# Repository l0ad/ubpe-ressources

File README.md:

# Ressources UBPE  

Ce dépôt contient des ressources (cartes capteurs, ...), utilisables dans le cadre de l'opération *Un ballon pour l'école* (UBPE) proposée par l'association [Planète-Sciences](https://www.planete-sciences.org/national/).

- [Cartes](./Cartes/README.md) 
	- capteurs analogiques
	- adaptateur pour étalonnage
	- conversion d'alimentation
	- ...
- ...

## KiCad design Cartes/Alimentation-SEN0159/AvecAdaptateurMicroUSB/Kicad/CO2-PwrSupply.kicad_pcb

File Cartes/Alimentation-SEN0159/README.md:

# Carte d'alimentation pour capteur CO2 SEN-0159

Version 1.1, novembre 2023.

*N.B.: les circuits utilisent les symboles/empreintes/modèles Kicad de la librairie additionnelle L0AD qui peut être téléchargée depuis ce [dépôt](https://github.com/l0ad/L0AD-kicad-library) et installée depuis le gestionnaire d'extensions Kicad (par fichier).* 

Cette carte est destinée à l'**alimentation** d'un module [module capteur de CO2 SEN0159](https://wiki.dfrobot.com/CO2_Sensor_SKU_SEN0159), et sa **connexion** à une carte *Kikiwi* (ou autre microcontrôleur).

Comme le capteur CO2 a besoin de préchauffer (et donc d'être alimenté) pendant plusieurs dizaines de minutes, il est ainsi possible d'alimenter le capteur temporairement avec une batterie externe via le port USB avant de le brancher de manière permanente à l'alimentation externe.

## Schéma de principe

La carte peut être alimentée soit via le connecteur externe (alimentation > 6V) ou directement en USB (5V). 

Le module *SEN-0159* est connecté via le connecteur JST-XH 3 points.

La carte est reliée au *Kikiwi* via le connecteur JST-XH 2 points (masse et signal uniquement, l'alimentation du capteur n'est pas prise du Kikiwi mais fournie par la carte).

La carte est conçue en deux variantes :

- avec un **connecteur MicroUSB** CMS
	- Le **projet Kicad** (>= v6.0) est disponible dans le répertoire [Kicad](./AvecConnecteurUSB/Kicad).
	- Les **fichiers de fabrication** sont disponibles dans le répertoire [Gerber](./AvecConnecteurUSB/Gerber). 
- avec un **adaptateur microUSB vers 2.54mm**, pour utiliser ce [module](https://www.amazon.fr/dp/B08ZML34CK).
	- Le **projet Kicad** (>= v6.0) est disponible dans le répertoire [Kicad](./AvecAdaptateurMicroUSB/Kicad).
	- Les **fichiers de fabrication** sont disponibles dans le répertoire [Gerber](./AvecAdaptateurMicroUSB/Gerber).

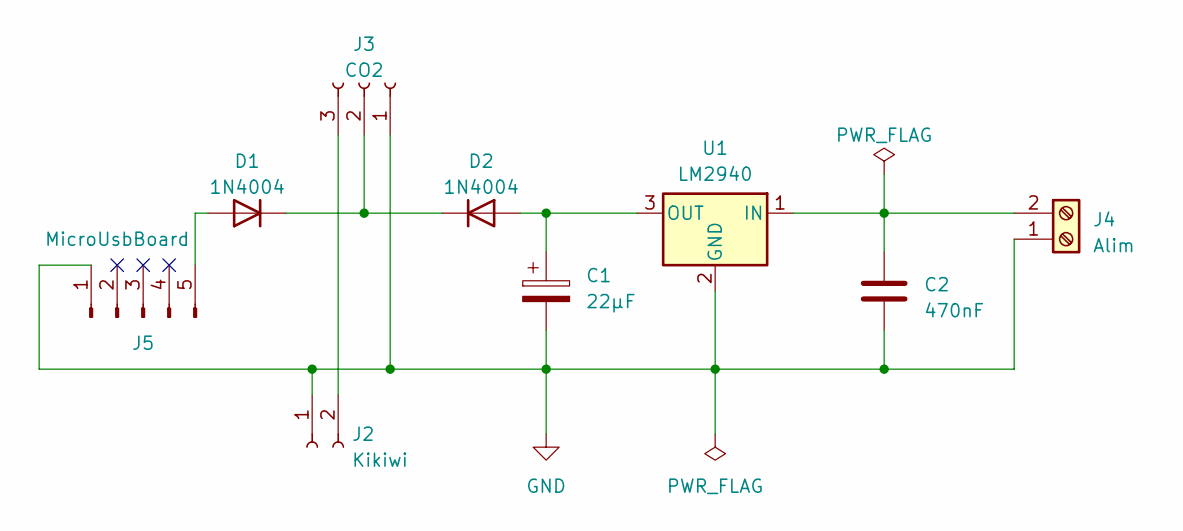
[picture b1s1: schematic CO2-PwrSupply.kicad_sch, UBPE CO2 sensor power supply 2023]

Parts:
C1: 22µF; CP_Radial_D5.0mm_P2.50mm
C2: 470nF; C_Rect_L7.0mm_W6.0mm_P5.00mm
D1, D2: 1N4004; D_DO-41_SOD81_P10.16mm_Horizontal
J2: Kikiwi; JST_XH_B2B-XH-A_1x02_P2.50mm_Vertical
J3: CO2; JST_XH_B3B-XH-A_1x03_P2.50mm_Vertical
J4: Alim; TerminalBlock_Phoenix_MKDS-1,5-2-5.08_1x02_P5.08mm_Horizont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
J5: MicroUsbBoard; PinHeader_1x05_P2.54mm_Vertical
U1: LM2940; TO-220-3_Horizontal_TabDown

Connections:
GND: C1.2, C2.2, J2.1, J3.1, J4.1, J5.1, U1.2 (GND)
unnamed: D1.2 (A), J5.5
unnamed: D1.1 (K), D2.1 (K), J3.2
unnamed: C1.1, D2.2 (A), U1.3 (OUT)
unnamed: J2.2, J3.3
unnamed: C2.1, J4.2, U1.1 (IN)

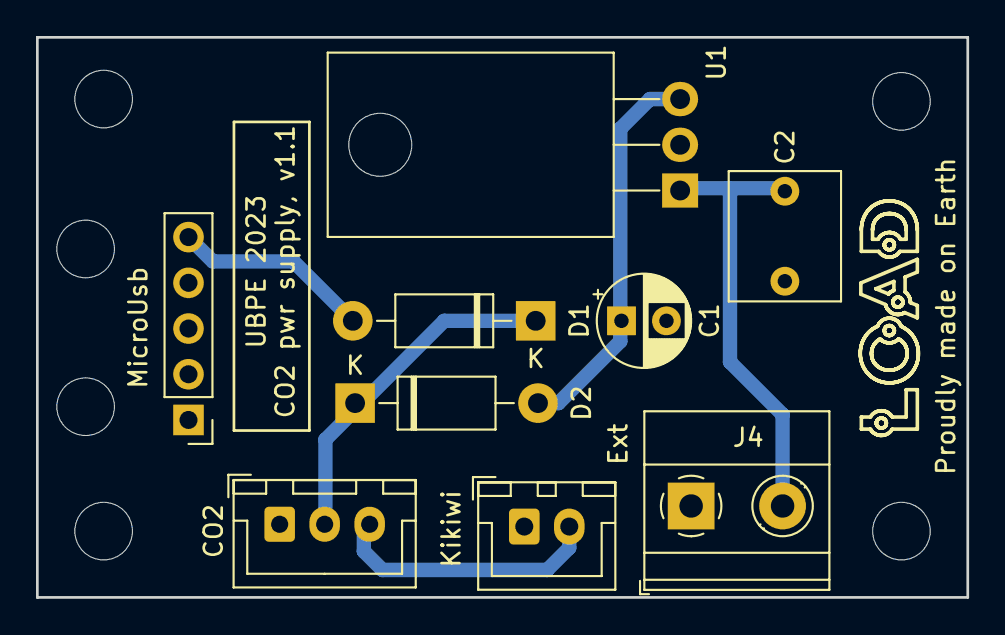
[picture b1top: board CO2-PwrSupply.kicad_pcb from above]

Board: 2 copper layers, 51.7 x 31.1 mm, 11 parts (1 on the bottom side), 6 nets.

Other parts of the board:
M3-1, M3-2: MountingHole_3.2mm_M3_ISO14580

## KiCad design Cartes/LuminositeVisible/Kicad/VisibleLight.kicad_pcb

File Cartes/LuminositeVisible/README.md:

# Capteur de luminosité (visible)

Version 1.1, novembre 2023.

*N.B.: les circuits utilisent les symboles/empreintes/modèles Kicad de la librairie additionnelle L0AD qui peut être téléchargée depuis ce [dépôt](https://github.com/l0ad/L0AD-kicad-library) et installée depuis le gestionnaire d'extensions Kicad (par fichier).* 

Cette carte peut être utilisée pour la mesure (analogique) luminosité (visible, proche IR),

## Schéma de principe

Le capteur utilisé est une **photodiode BPW34** (voir [datasheet](https://www.vishay.com/docs/81521/bpw34.pdf)

La tension d'alimentation est 3.3V, la connectique est de type JST-XH 3 points pour la liaison avec la carte Tenum/Planete-sciences *Kikiwi*, un micro-controleur ou un adaptateur destiné à l'étalonnage.

La diode peut être soit soudée sur la carte (surélevée et/ou montée à l'envers pour dépasser du dos de la carte) ou déportée à l'aide du connecteur 2 broches.

Les connecteurs peuvent être au choix horizontaux ou verticaux.

- Le **projet Kicad** (>= v6.0) est disponible dans le répertoire [Kicad](./Kicad).
- Les **fichiers de fabrication** sont disponibles dans le répertoire [Gerber](./Gerber).

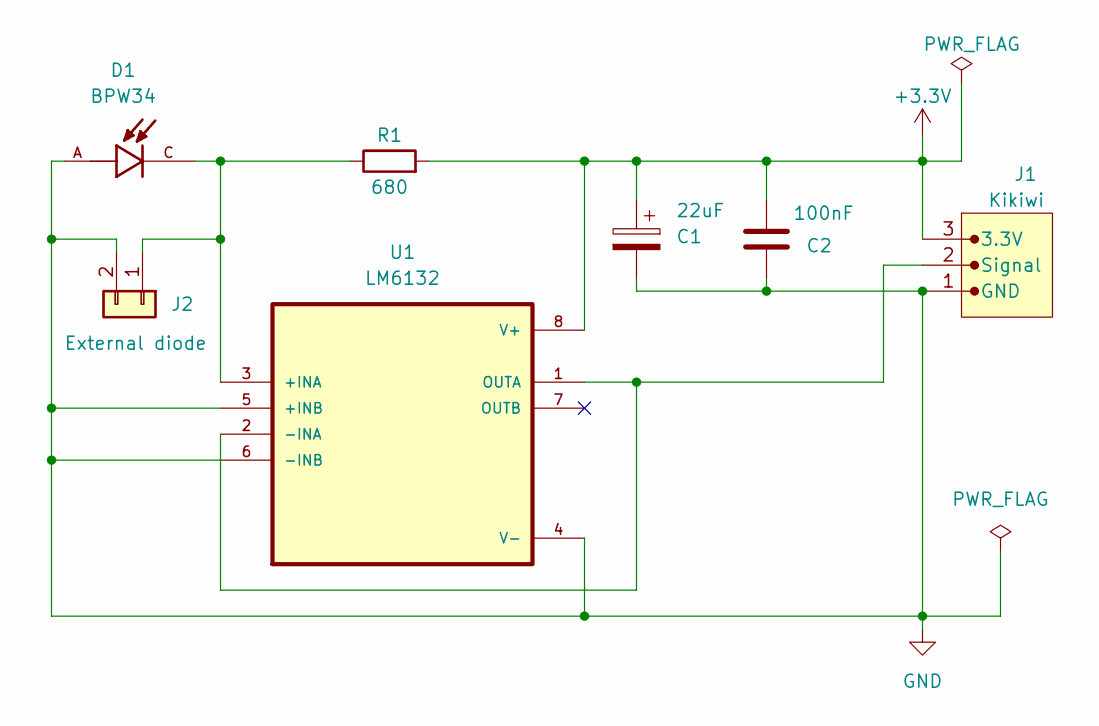
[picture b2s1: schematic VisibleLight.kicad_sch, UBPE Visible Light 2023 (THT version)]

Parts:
C1: 22uF; CP_Radial_D5.0mm_P2.50mm
C2: 100nF; C_Rect_L7.0mm_W2.5mm_P5.00mm
D1: BPW34; PARTREV 2.1
J1: Kikiwi; JST_XH_B3B-XH-AM_1x03_P2.50mm_Vertical
J2: External diode; JST_XH_B2B-XH-A_1x02_P2.50mm_Vertical
R1: 680; R_Axial_DIN0204_L3.6mm_D1.6mm_P7.62mm_Horizontal
U1: LM6132; DIP-8_W7.62mm

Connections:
+3.3V: C1.1, C2.2, J1.3 (3.3V), R1.2, U1.8 (V+)
GND: C1.2, C2.1, D1.A, J1.1 (GND), J2.2, U1.4 (V-), U1.5 (+INB), U1.6 (-INB)
unnamed: J1.2 (Signal), U1.1 (OUTA), U1.2 (-INA)
unnamed: D1.C, J2.1, R1.1, U1.3 (+INA)

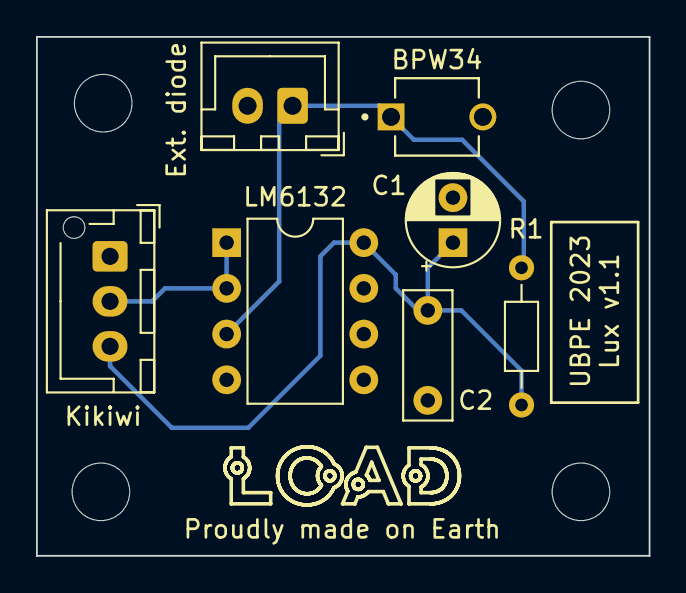
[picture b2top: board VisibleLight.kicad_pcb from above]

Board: 2 copper layers, 34.0 x 28.8 mm, 7 parts (0 on the bottom side), 4 nets.

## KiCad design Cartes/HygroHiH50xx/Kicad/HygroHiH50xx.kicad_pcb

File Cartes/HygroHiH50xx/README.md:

# Carte capteur d'humidité (HiH-50xx)

Version 1.1, novembre 2023.

*N.B.: les circuits utilisent les symboles/empreintes/modèles Kicad de la librairie additionnelle L0AD qui peut être téléchargée depuis ce [dépôt](https://github.com/l0ad/L0AD-kicad-library) et installée depuis le gestionnaire d'extensions Kicad (par fichier).* 

Cette carte peut être utilisée pour la mesure (analogique) d'humidité relative de l'air.

## Schéma de principe

Le capteur utilisé est de type **HiH-50xx** (voir [datasheet](https://prod-edam.honeywell.com/content/dam/honeywell-edam/sps/siot/fr-fr/products/sensors/humidity-with-temperature-sensors/hih-5030-5031-series/documents/sps-siot-hih5030-5031-series-product-sheet-009050-2-en-ciid-49692.pdf))

La tension d'alimentation est 3.3V, la connectique est de type JST-XH 3 points pour la liaison avec la carte Tenum/Planete-sciences *Kikiwi*, un micro-controleur ou un adaptateur destiné à l'étalonnage.

- Le **projet Kicad** (>= v6.0) est disponible dans le répertoire [Kicad](./Kicad).
- Les **fichiers de fabrication** sont disponibles dans le répertoire [Gerber](./Gerber).

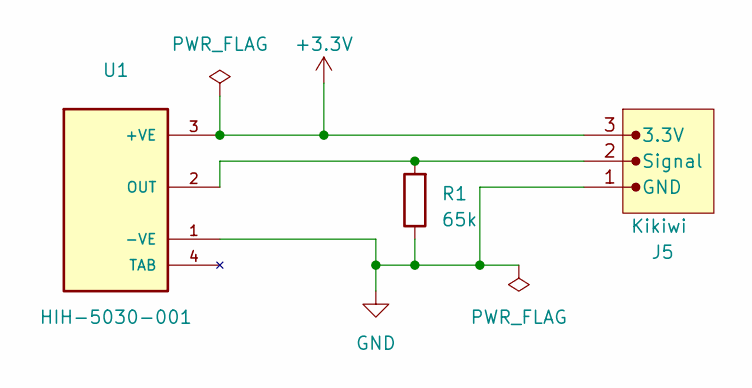
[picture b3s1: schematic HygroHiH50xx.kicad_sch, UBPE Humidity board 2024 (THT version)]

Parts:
J5: Kikiwi; JST_XH_B3B-XH-A_1x03_P2.50mm_Vertical
R1: 65k; R_Axial_DIN0207_L6.3mm_D2.5mm_P10.16mm_Horizontal
U1: HIH-5030-001; HiH-5030

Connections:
+3.3V: J5.3, U1.3 (+VE)
GND: J5.1, R1.1, U1.1 (-VE)
unnamed: J5.2, R1.2, U1.2 (OUT)

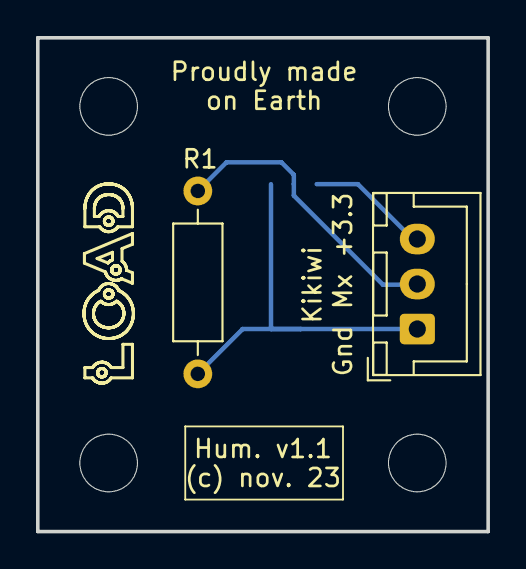
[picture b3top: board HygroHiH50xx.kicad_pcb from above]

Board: 2 copper layers, 25.0 x 27.4 mm, 3 parts (1 on the bottom side), 3 nets.

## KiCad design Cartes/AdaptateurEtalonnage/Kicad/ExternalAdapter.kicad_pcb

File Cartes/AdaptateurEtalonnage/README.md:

# Adaptateur pour l'étalonnage

Version 1.0, novembre 2023.

*N.B.: les circuits utilisent les symboles/empreintes/modèles Kicad de la librairie additionnelle L0AD qui peut être téléchargée depuis ce [dépôt](https://github.com/l0ad/L0AD-kicad-library) et installée depuis le gestionnaire d'extensions Kicad (par fichier).* 

Cette carte est destinée à l'étalonnage des capteurs analogiques, elle ne comporte aucun composant actif mais seulement de la connectique.

L'alimentation s'effectue en 3.3V, la connectique *JST-XH* 3 points permet la liaison avec le capteur, la connectique *SLB4* 1 point permet l'alimentation et la prise de mesure.

- Le **projet Kicad** (>= v6.0) est disponible dans le répertoire [Kicad](./Kicad).
- Les **fichiers de fabrication** sont disponibles dans le répertoire [Gerber](./Gerber).

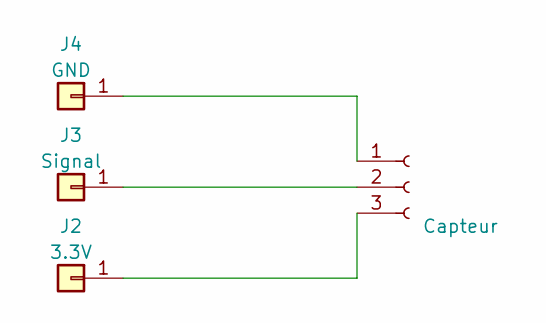
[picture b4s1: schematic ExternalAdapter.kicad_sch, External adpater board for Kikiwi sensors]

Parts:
J1: Capteur; JST_XH_S3B-XH-A-1_1x03_P2.50mm_Horizontal
J2: 3.3V; SolderWire-1.5sqmm_1x01_D1.7mm_OD3.9mm
J3: Signal; SolderWire-1.5sqmm_1x01_D1.7mm_OD3.9mm
J4: GND; SolderWire-1.5sqmm_1x01_D1.7mm_OD3.9mm

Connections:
unnamed: J1.1, J4.1
unnamed: J1.2, J3.1
unnamed: J1.3, J2.1

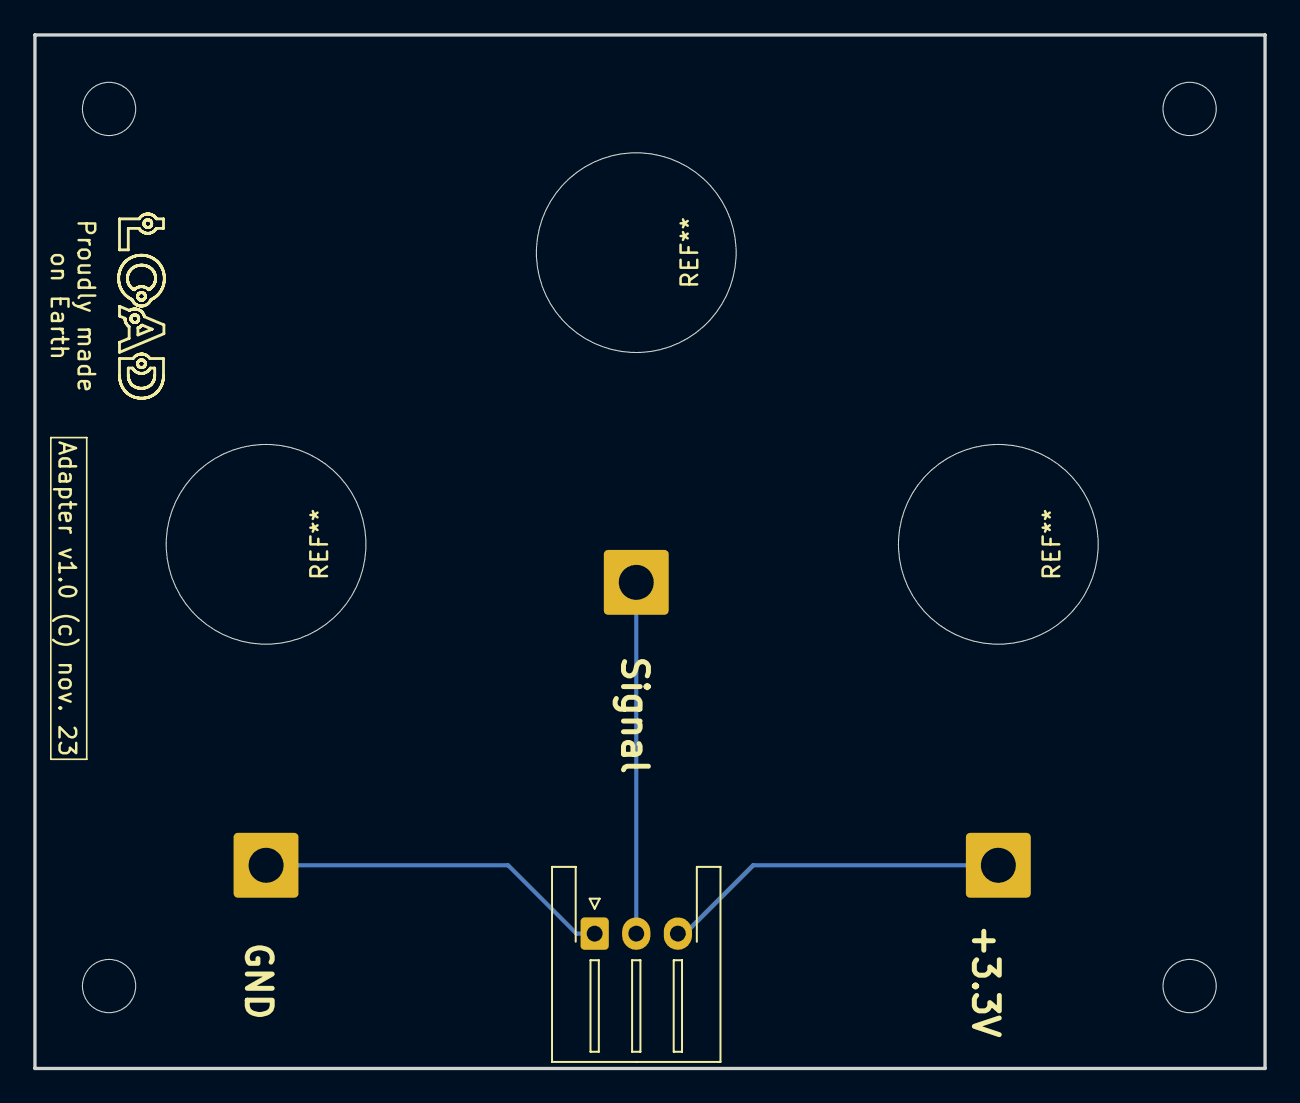
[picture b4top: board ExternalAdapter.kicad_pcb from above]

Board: 2 copper layers, 73.9 x 62.1 mm, 4 parts (0 on the bottom side), 3 nets.

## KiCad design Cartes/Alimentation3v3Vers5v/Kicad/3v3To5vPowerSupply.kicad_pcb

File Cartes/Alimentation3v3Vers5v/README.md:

# Carte de conversion d'alimentation (3.3V vers 5V)

Version 1.0, décembre 2023.

- *N.B.: le circuit utilise les symboles/empreintes/modèles de la librairie additionnelle L0AD qui peut être téléchargée depuis ce [dépôt](https://github.com/l0ad/L0AD-kicad-library) et installée depuis le gestionnaire d'extensions Kicad (par fichier).* 

Carte carte est destinée à connecter à la carte *Kikiwi* des capteurs nécessitant une tension d'alimentation de 5v.

## Schéma de principe

L'alimentation est fournie par la carte Tenum/Planete-Sciences *Kikiwi*, qui délivre 3.3V. certains capteurs nécessitent une tension supérieure pour fonctionner correctement. 

Par conséquent, le circuit utilise un **doubleur de tension** (basé sur un ILC7660) et un régulateur **LDO** 5V. 

Le régulateur utilisé est un modèle de la série *MCP-170x-5002* mais il peut être remplacé par n'importe quel autre LDO à conditions que celui-ci soit compatible broche-à-broche et qu'il ait une chute de tension inférieure à 200 mV sous un courant de sorte de 50 mA.

Le filtre anti-bruit peut être partiellement retiré si besoin (ferrite et condensateur suivant). Dans ce cas, un cavalier doit être placé sur le connecteur de shunt.

- Le **projet Kicad** (>= v6.0) est disponible dans le répertoire [Kicad](./Kicad).
- Les **fichiers de fabrication** sont disponibles dans le répertoire [Gerber](./Gerber).

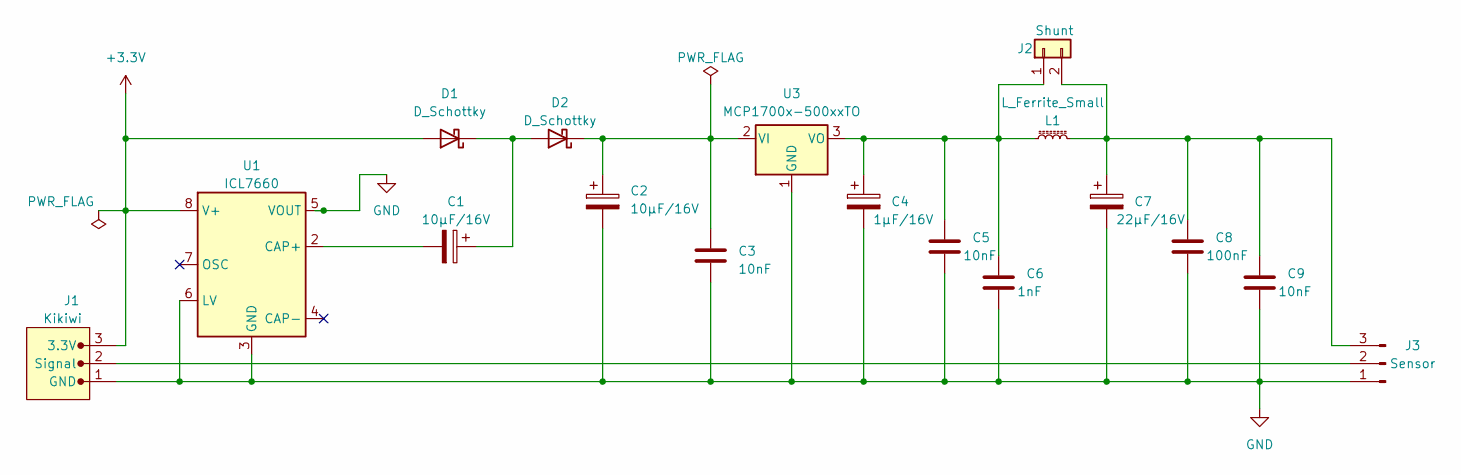
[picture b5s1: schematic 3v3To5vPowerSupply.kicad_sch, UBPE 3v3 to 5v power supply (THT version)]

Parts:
C1, C2: 10µF/16V; CP_Radial_Tantal_D4.5mm_P2.50mm
C3, C5, C9: 10nF; C_Disc_D4.7mm_W2.5mm_P5.00mm
C4: 1µF/16V; CP_Radial_Tantal_D4.5mm_P2.50mm
C6: 1nF; C_Rect_L7.0mm_W2.0mm_P5.00mm
C7: 22µF/16V; CP_Radial_Tantal_D5.0mm_P2.50mm
C8: 100nF; C_Rect_L7.0mm_W2.0mm_P5.00mm
D1, D2: D_Schottky; D_T-1_P5.08mm_Horizontal
J1: Kikiwi; JST_XH_B3B-XH-A_1x03_P2.50mm_Vertical
J2: Shunt; PinHeader_1x02_P2.54mm_Vertical
J3: Sensor; JST_XH_B3B-XH-A_1x03_P2.50mm_Vertical
L1: L_Ferrite_Small; L_1206_3216Metric_Pad1.42x1.75mm_HandSolder
U1: ICL7660; DIP-8_W7.62mm
U3: MCP1700x-500xxTO; TO-92_Inline

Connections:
+3.3V: D1.2 (A), J1.3 (3.3V), U1.8 (V+)
GND: C2.2, C3.2, C4.2, C5.2, C6.2, C7.2, C8.2, C9.2, J1.1 (GND), J3.1, U1.3 (GND), U1.5 (VOUT), U1.6 (LV), U3.1 (GND)
unnamed: C1.1, D1.1 (K), D2.2 (A)
unnamed: C2.1, C3.1, D2.1 (K), U3.2 (VI)
unnamed: J1.2 (Signal), J3.2
unnamed: C4.1, C5.1, C6.1, J2.1, L1.1, U3.3 (VO)
unnamed: C7.1, C8.1, C9.1, J2.2, J3.3, L1.2
unnamed: C1.2, U1.2 (CAP+)

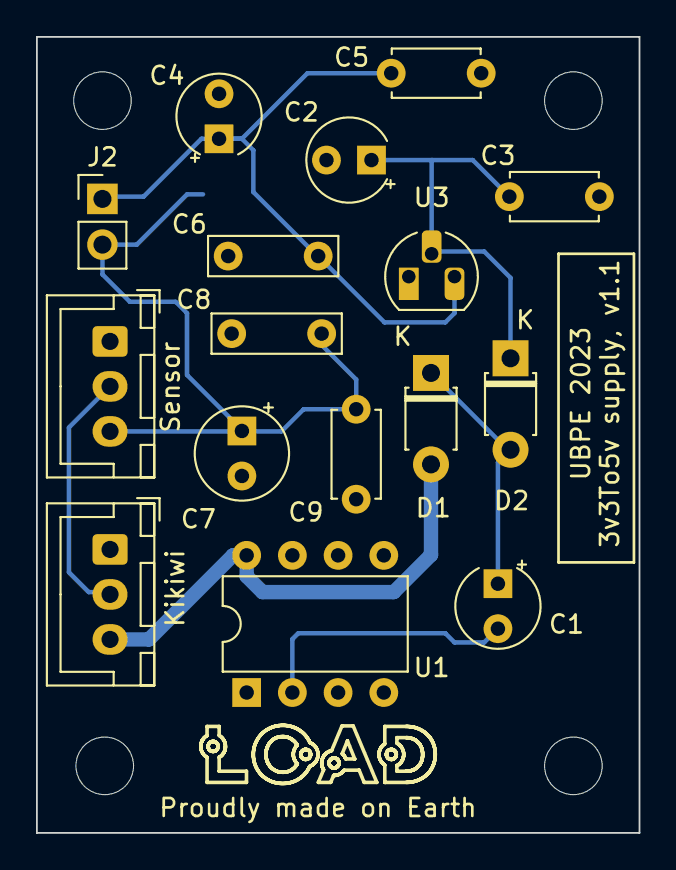
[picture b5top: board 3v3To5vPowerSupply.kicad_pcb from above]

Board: 2 copper layers, 33.5 x 44.2 mm, 17 parts (1 on the bottom side), 8 nets.

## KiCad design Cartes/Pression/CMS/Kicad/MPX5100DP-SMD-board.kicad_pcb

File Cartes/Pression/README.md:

# Capteur de pression MPX5100DP

Version 1.2, novembre 2023.

*N.B.: les circuits utilisent les symboles/empreintes/modèles Kicad de la librairie additionnelle L0AD qui peut être téléchargée depuis ce [dépôt](https://github.com/l0ad/L0AD-kicad-library) et installée depuis le gestionnaire d'extensions Kicad (par fichier).* 

Cette carte peut être utilisée pour la mesure (analogique) de pression.

## Schéma de principe

Le capteur utilisé est un capteur de pression différentiel **MPX5100DP** (voir [datasheet](https://www.nxp.com/docs/en/data-sheet/MPX5100.pdf). 

*N.B. Le choix d'un capteur différentiel est motivé par sa cpacité à mesurer des différences de pression très faibles, le rendant plus adapté qu'un modèle absolu saturant plus rapidement.
*
L'alimentation est fournie par la carte Tenum/Planete-Sciences *Kikiwi*, qui délivre 3.3V. Le capteur nécessite une tension supérieure pour fonctionner correctement. Par conséquent, le circuit utilise un **doubleur de tension** (basé sur un ILC7660) et un régulateur **LDO** 5V. 

Le régulateur utilisé est un modèle de la série *MCP-170x-5002* mais il peut être remplacé par n'importe quel autre LDO à conditions que celui-ci soit compatible broche-à-broche et qu'il ait une chute de tension inférieure à 200 mV sous un courant de sorte de 50 mA.

Le filtre anti-bruit peut être partiellement retiré si besoin (ferrite et condensateur suivant). Dans ce cas, un cavalier doit être placé sur le connecteur de shunt.

Cette carte a été conçue en deux variantes :

- (presque) uniquement avec des composants traversants
	- Le **projet Kicad** (>= v6.0) est disponible dans le répertoire [Kicad](./THT/Kicad).
	- Les **fichiers de fabrication** sont disponibles dans le répertoire [Gerber](./THT/Gerber).
- avec des composants montés en surface
	- Le **projet Kicad** (>= v6.0) est disponible dans le répertoire [Kicad](./CMS/Kicad).
	- Les **fichiers de fabrication** sont disponibles dans le répertoire [Gerber](./CMS/Gerber).

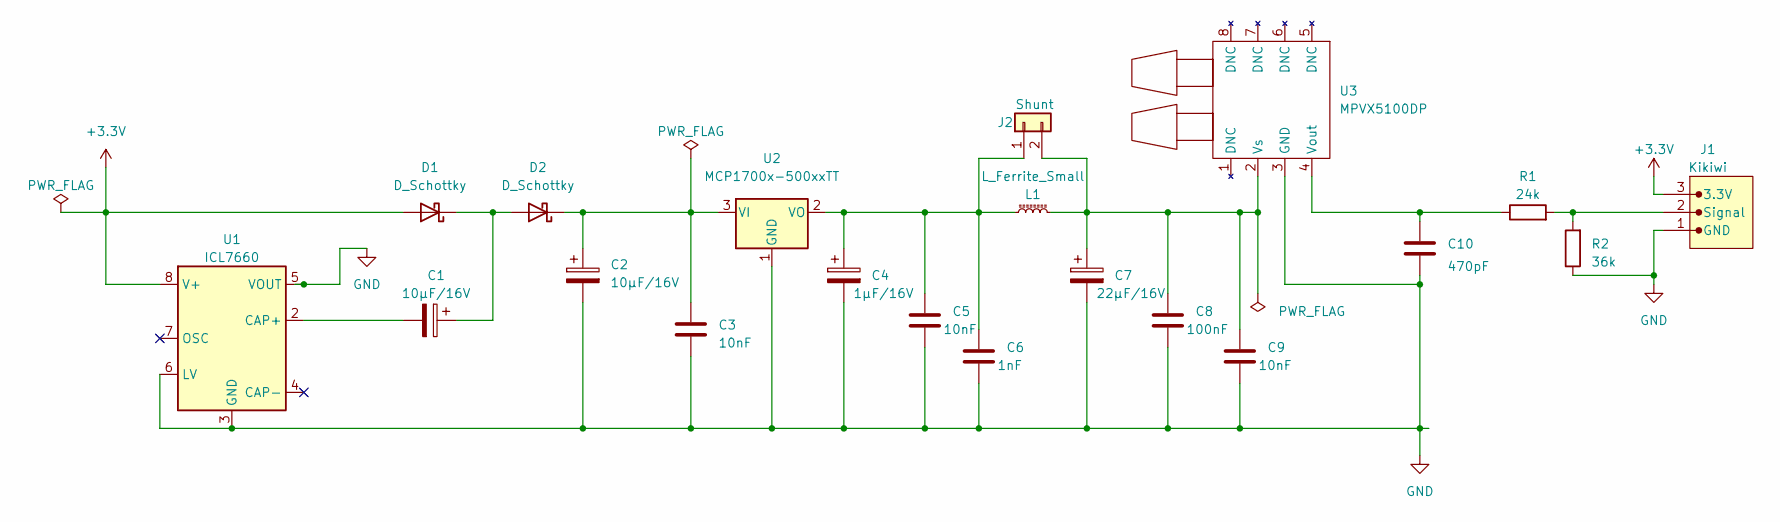
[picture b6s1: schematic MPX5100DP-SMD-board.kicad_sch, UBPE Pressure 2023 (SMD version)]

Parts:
C1, C2: 10µF/16V; CP_EIA-3528-21_Kemet-B_Pad1.50x2.35mm_HandSolder
C3, C5, C9: 10nF; C_0805_2012Metric_Pad1.18x1.45mm_HandSolder
C4: 1µF/16V; CP_EIA-3216-18_Kemet-A_Pad1.58x1.35mm_HandSolder
C6: 1nF; C_0805_2012Metric_Pad1.18x1.45mm_HandSolder
C7: 22µF/16V; CP_EIA-6032-28_Kemet-C_Pad2.25x2.35mm_HandSolder
C8: 100nF; C_0805_2012Metric_Pad1.18x1.45mm_HandSolder
C10: 470pF; C_0805_2012Metric_Pad1.18x1.45mm_HandSolder
D1, D2: D_Schottky; D_0603_1608Metric_Pad1.05x0.95mm_HandSolder
J1: Kikiwi; JST-XH-3P_SMD_H
J2: Shunt; PinHeader_1x02_P2.54mm_Vertical_SMD_Pin1Left
L1: L_Ferrite_Small; L_0805_2012Metric_Pad1.15x1.40mm_HandSolder
R1: 24k; R_0805_2012Metric_Pad1.20x1.40mm_HandSolder
R2: 36k; R_0805_2012Metric_Pad1.20x1.40mm_HandSolder
U1: ICL7660; SOIC-8_3.9x4.9mm_P1.27mm
U2: MCP1700x-500xxTT; SOT-23
U3: MPVX5100DP; MPXV5100DP

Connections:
+3.3V: D1.2 (A), J1.3 (3.3V), U1.8 (V+)
GND: C2.2, C3.2, C4.2, C5.2, C6.2, C7.2, C8.2, C9.2, C10.2, J1.1 (GND), R2.1, U1.3 (GND), U1.5 (VOUT), U1.6 (LV), U2.1 (GND), U3.3 (GND)
unnamed: C1.1, D1.1 (K), D2.2 (A)
unnamed: C2.1, C3.1, D2.1 (K), U2.3 (VI)
unnamed: J1.2 (Signal), R1.2, R2.2
unnamed: C4.1, C5.1, C6.1, J2.1, L1.1, U2.2 (VO)
unnamed: C7.1, C8.1, C9.1, J2.2, L1.2, U3.2 (Vs)
unnamed: C1.2, U1.2 (CAP+)
unnamed: C10.1, R1.1, U3.4 (Vout)

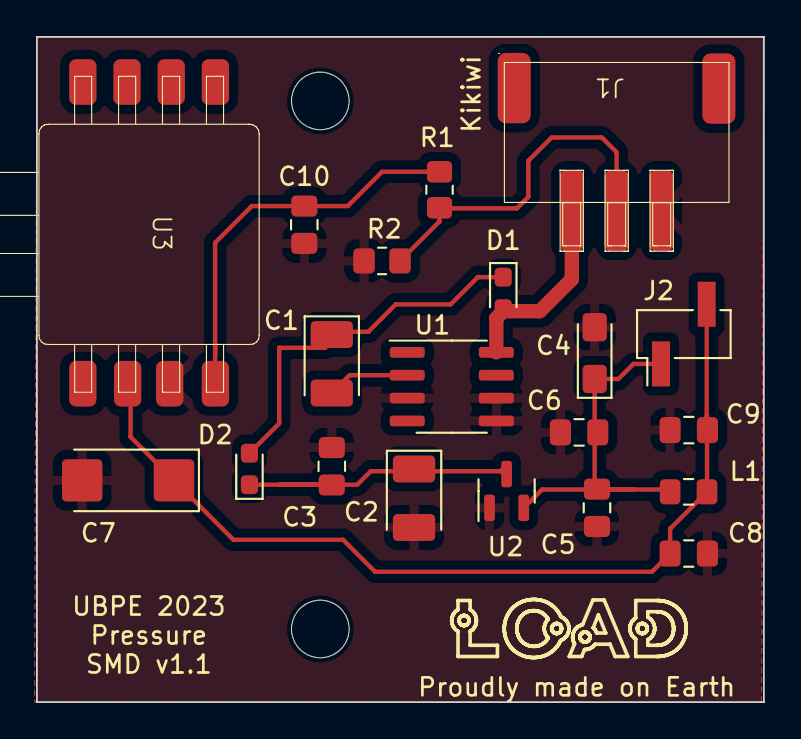
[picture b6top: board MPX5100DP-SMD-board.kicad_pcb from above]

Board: 2 copper layers, 40.4 x 37.0 mm, 20 parts (0 on the bottom side), 9 nets.

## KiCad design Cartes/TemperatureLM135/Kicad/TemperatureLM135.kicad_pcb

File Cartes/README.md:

# Cartes

Cette section regroupe des **cartes capteurs analogiques** intialement conçues pour être connectées sur une carte Kikiwi (mais peuvent également être connectées à un microcontroleur de type Arduino ou autre), de même que des cartes destinées à l'**étalonnage** ou l'**alimentation**.

- [Capteur de température LM135](./TemperatureLM135/README.md)
- [Capteur d'humidité HiH50xx](./HygroHiH50xx/README.md)
- [Capteur de luminosité visible](./LuminositeVisible/README.md)
- [Capteur de pression](./Pression/README.md)
- [Carte d'alimentation/connexion pour capteur CO2 SEN-0159](./Alimentation-SEN0159/README.md)
- [Adaptateur pour étalonnage](./AdaptateurEtalonnage/README.md)
- [Convertisseur d'alimentation 3v3 vers 5v](./Alimentation3v3Vers5v/README.md)

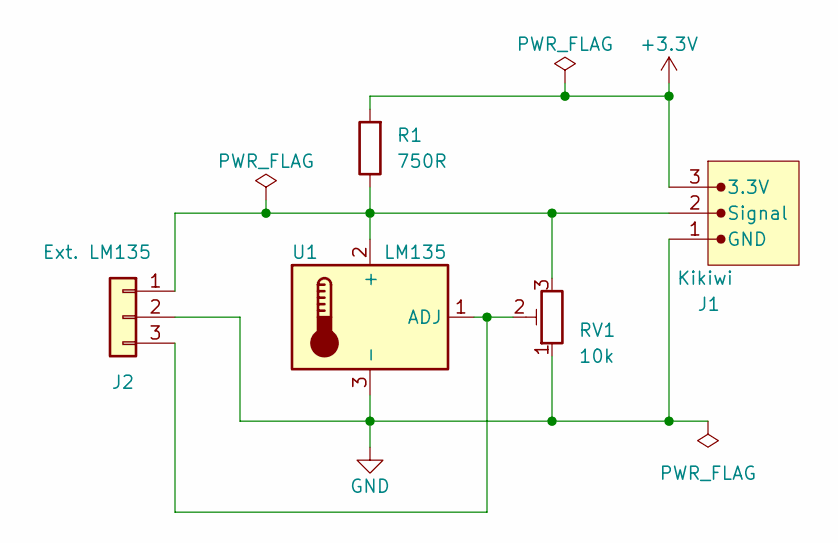
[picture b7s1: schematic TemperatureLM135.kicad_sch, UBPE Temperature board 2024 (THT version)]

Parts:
J1: Kikiwi; JST_XH_B3B-XH-A_1x03_P2.50mm_Vertical
J2: Ext. LM135; JST_XH_B3B-XH-A_1x03_P2.50mm_Vertical
R1: 750R; R_Axial_DIN0207_L6.3mm_D2.5mm_P10.16mm_Horizontal
RV1: 10k; Potentiometer_Runtron_RM-065_Vertical
U1: LM135; TO-92_Wide

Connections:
+3.3V: J1.3 (3.3V), R1.2
GND: J1.1 (GND), J2.2, RV1.1, U1.3 (-)
unnamed: J1.2 (Signal), J2.1, R1.1, RV1.3, U1.2 (+)
unnamed: J2.3, RV1.2, U1.1 (ADJ)

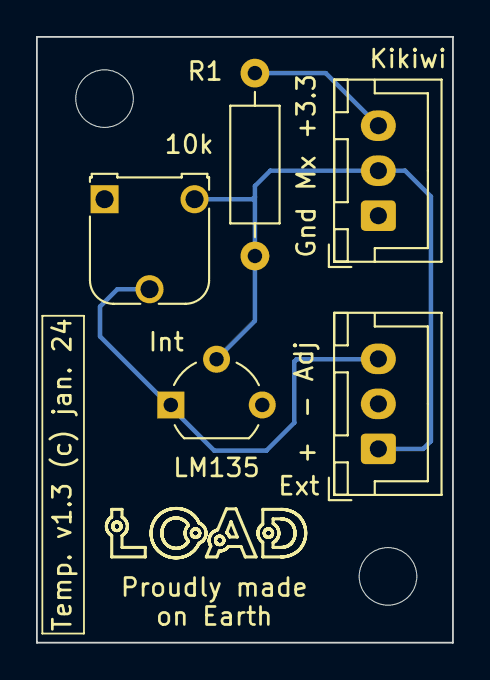
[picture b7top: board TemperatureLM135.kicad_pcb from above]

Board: 2 copper layers, 23.1 x 33.7 mm, 5 parts (0 on the bottom side), 4 nets.

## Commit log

2024-12-06 Commit initial
